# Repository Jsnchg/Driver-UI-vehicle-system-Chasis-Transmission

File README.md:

# Driver-UI-vehicle-system-Chasis-Transmission

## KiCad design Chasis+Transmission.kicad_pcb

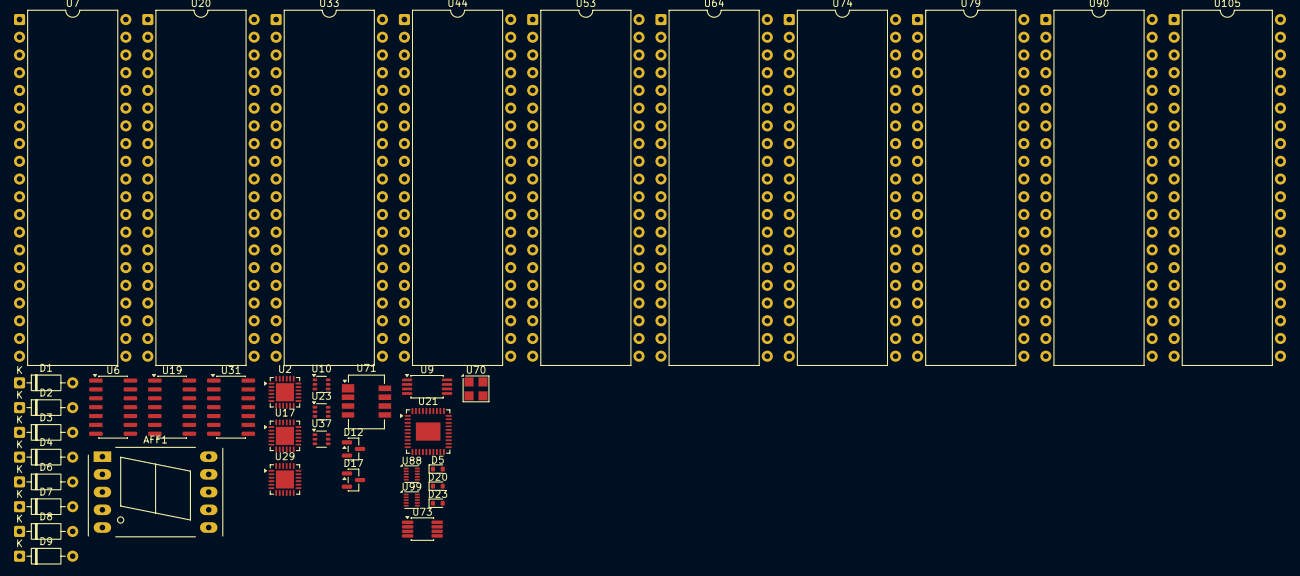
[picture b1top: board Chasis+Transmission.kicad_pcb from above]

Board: 2 copper layers, 40 parts (0 on the bottom side), 45 nets, no tracks yet.

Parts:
AFF1: LTS-6980HR; 7SegmentLED_LTS6760_LTS6780
D1, D2, D3, D4, D6, D7, D8, D9: DSB5712; D_DO-35_SOD27_P7.62mm_Horizontal
D5, D20, D23: 1N4148WT; D_SOD-523
D12, D17: BAT54C; SOT-23
U2, U17, U29: LTC4417CUF; QFN-24-1EP_4x4mm_P0.5mm_EP2.6x2.6mm
U6, U19, U31: TCAN1043xDxQ1; SOIC-14_3.9x8.7mm_P1.27mm
U7, U20, U33, U44, U53, U64, U74, U79, U90, U105: 8080; DIP-40_W15.24mm
U9: CDCV304; TSSOP-8_4.4x3mm_P0.65mm
U10, U23, U37: NCS210; SOT-363_SC-70-6
U21: DRV8308; Texas_RHA0040E_VQFN-40-1EP_6x6mm_P0.5mm_EP3.52x2.62mm
U70: MS5837-xxBA; TE_MS5837-xxBA
U71: SHT1x
U73: ADC082S021; VSSOP-8_3x3mm_P0.65mm
U88, U99: MMA8653FCR1; DFN-10_2x2mm_P0.4mm

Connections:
+12V: U64.13 (HOLD), U64.14 (INT), U64.23 (READY)
GND: U21.26 (GND), U21.41 (GND)
unnamed: D1.1 (K), D3.1 (K), U2.1 (UV1)
unnamed: D2.1 (K), D4.1 (K), U6.1 (TXD)
unnamed: D6.1 (K), D8.1 (K), U17.25 (PAD)
unnamed: D7.1 (K), D9.1 (K), U19.1 (TXD)
unnamed: U79.1 (A10), U79.40 (A11)
unnamed: U90.2 (GND), U90.11 (-5V)
unnamed: D20.2 (A), U90.37 (A12), U90.40 (A11)
unnamed: U53.12 (RESET), U53.13 (HOLD), U53.14 (INT), U53.15 (ϕ2), U53.22 (ϕ1), U53.23 (READY)
unnamed: U2.17 (G1), U2.18 (VS1)
unnamed: U6.3 (VCC), U6.5 (VIO), U6.10 (VSUP)
unnamed: U7.28 (+12V), U9.6 (V_{DD})
unnamed: U7.25 (A0), U9.8 (1Y3)
unnamed: U7.26 (A1), U9.7 (1Y2)
unnamed: U7.27 (A2), U9.5 (1Y1)
unnamed: U7.29 (A3), U9.3 (1Y0)
unnamed: U7.30 (A4), U10.4 (+IN)
unnamed: U7.31 (A5), U10.5 (-IN)
unnamed: U17.1 (UV1), U17.2 (OV1), U17.3 (UV2), U17.4 (OV2), U17.5 (UV3), U17.6 (OV3), U17.19 (V3), U17.20 (V2), U17.21 (V1), U17.22 (EN), U17.23 (~SHDN), U17.24 (HYS)
unnamed: U17.12 (VOUT), U17.13 (G3), U17.14 (VS3), U17.15 (G2), U17.16 (VS2), U17.17 (G1), U17.18 (VS1)
unnamed: U19.3 (VCC), U19.5 (VIO), U19.10 (VSUP)
unnamed: U20.4 (D5), U23.3 (Vs)
unnamed: U20.5 (D6), U23.4 (+IN)
unnamed: U20.6 (D7), U23.5 (-IN)
unnamed: U20.17 (DBIN), U21.2 (UHN)
unnamed: U20.18 (~WR), U21.1 (UHP)
unnamed: U29.1 (UV1), U29.2 (OV1), U29.3 (UV2), U29.4 (OV2), U29.5 (UV3), U29.6 (OV3), U29.19 (V3), U29.20 (V2), U29.21 (V1), U29.22 (EN), U29.23 (~SHDN), U29.24 (HYS)
unnamed: U29.12 (VOUT), U29.13 (G3), U29.14 (VS3), U29.15 (G2), U29.16 (VS2), U29.17 (G1), U29.18 (VS1)
unnamed: U31.3 (VCC), U31.5 (VIO), U31.10 (VSUP)
unnamed: U33.10 (D0), U33.25 (A0), U33.26 (A1)
unnamed: U33.7 (D3), U33.9 (D1)
unnamed: U33.4 (D5), U37.3 (Vs)
unnamed: U33.5 (D6), U37.4 (+IN)
unnamed: U33.6 (D7), U37.5 (-IN)
unnamed: U33.14 (INT), U33.23 (READY)
unnamed: U70.1 (GND), U71.1 (GND)
unnamed: U70.3 (SCL), U73.3 (GND), U74.2 (GND), U74.11 (-5V)
unnamed: U70.4 (SDA), U71.2 (DATA)
unnamed: U73.6 (DIN), U74.23 (READY)
unnamed: U73.7 (DOUT), U74.14 (INT)
unnamed: U73.8 (SCLK), U74.13 (HOLD)
unnamed: D17.2, D17.3
unnamed: U88.6 (GND), U88.7 (GND), U88.9 (GND)
unnamed: U99.6 (GND), U99.7 (GND), U99.9 (GND)
